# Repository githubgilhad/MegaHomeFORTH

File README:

Mega Home Computer with FORTH - based on ATmega2560 - step to graphic card for HD6309 - VGA, RCA, PS/2

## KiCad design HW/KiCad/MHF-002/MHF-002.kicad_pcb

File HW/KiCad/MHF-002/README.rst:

.. vim: ft=rst noexpandtab fileencoding=utf-8 nomodified   wrap textwidth=0 foldmethod=marker foldmarker={{{,}}} foldcolumn=4 ruler showcmd lcs=tab\:|- list tabstop=8 noexpandtab nosmarttab softtabstop=0 shiftwidth=0 linebreak showbreak=--»\ 

.. |Ohm| raw:: html

	Ω

.. |kOhm| raw:: html

	kΩ

|MemxFORTHChipandColorfulStack.png|

MegaHomeFORTH MHF-002
=====================

This is next iteration of `MegaHomeFORTH MHF-001 <https://github.com/githubgilhad/MegaHomeFORTH/tree/MHF-001>`__

MHF-001 was sponsored by PCBway.com, which generously manufactured the PCB for it as sponsorship. The PCB was perfectly done and allowed for testings and rewiring problematic parts to reveal hidden problems in the first iteration design.

MHF-002 have more than 75 improvements over MHF-001 and should be even more testable and more convenient for hand soldering, while using more modern parts.

Global Goals
============

|MHF-002.png|

|MHF-002.a.s.jpg|

|MHF-002.b.s.jpg|

MHF was created as an implementation of a graphical and I/O card design for an 8-bit computer based on the HD6309 processor (hereafter referred to as CPU). The actual design is built around the ATmega2560 microcontroller (used, for example, in the Arduino Mega), which I will refer to as the MCU. The MCU is supplemented with RAM and several simple circuits for input and output. Another RAM chip is used for data transfer in both directions, shared alternately between the CPU and MCU. The advantage of this design is high throughput (at the cost of latency) and easy access from both systems.

During the debugging of the preliminary prototypes, it proved to be a significant advantage to have interactive access to the hardware, which led to the implementation of FORTH. It also became clear that, in addition to VGA/RCA, the PS/2 keyboard and SD card could be read concurrently. With enough memory, the graphics card can even function as a standalone single-board computer (SBC), which is a more convenient mode for debugging.

Since access to the shared RAM requires cooperation with the GLUE, the board also includes jumpers for easy configuration of the SBC mode, where some signals intended for the SysBus are redirected directly to the shared memory.

Detailed configuration and usage options will be described on a separate page, but for a quick start, it is sufficient to solder either the left or right side of the A/B jumpers for the graphics card mode. For SBC mode, it is enough to solder the SBC jumpers. These options are mutually exclusive (either graphics card mode or SBC).

Next, there are previews of MHF-002 and links to the schematic and PCB (only the top and bottom layers, as both middle layers are reserved for power), which were generated from KiCad files.

.. |MHF-002.a.s.jpg| image:: MHF-002.a.s.jpg
	:width: 250
	:align: top
	:target: MHF-002.a.s.jpg

.. |MHF-002.b.s.jpg| image:: MHF-002.b.s.jpg
	:width: 250
	:align: top
	:target: MHF-002.b.s.jpg

.. |MHF-002.png| image:: MHF-002.png
	:width: 250
	:align: top
	:target: MHF-002.png

.. |MemxFORTHChipandColorfulStack.png| image:: MemxFORTHChipandColorfulStack.png
	:width: 250
	:align: top
	:target: MemxFORTHChipandColorfulStack.png

.. |view.bottom.png| image:: view.bottom.png
	:width: 250
	:align: top
	:target: view.bottom.png

.. |view_1.png| image:: view_1.png
	:width: 250
	:align: top
	:target: view_1.png

.. |view_2.png| image:: view_2.png
	:width: 250
	:align: top
	:target: view_2.png

.. |view_top.png| image:: view_top.png
	:width: 250
	:align: top
	:target: view_top.png

|view_top.png|

|view.bottom.png|

|view_1.png|

|view_2.png|

`Schema <schema.pdf>`__

`PCB <pcb.pdf>`__

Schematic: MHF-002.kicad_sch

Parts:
C1: 10nF; C_Disc_D4.3mm_W1.9mm_P5.00mm
C2, C5, C6, C7, C8, C10, C15, C16: 100n; C_0805_2012Metric_HandSolder
C3, C4: 22n; C_0805_2012Metric_HandSolder
C9: DTR 100n; C_Disc_D3.0mm_W2.0mm_P2.50mm
C11: 10M; C_0805_2012Metric_HandSolder
C12: 100n RESET; C_Disc_D3.0mm_W2.0mm_P2.50mm
C13, C14: 22p; C_0805_2012Metric_HandSolder
Cx1, Cx2, Cx3, Cx4, Cx5, Cx6, Cx7, Cx8, Cx9, Cx10, Cx11, Cx12, Cx13, Cx16, Cx17, Cx18: Cx; C_Disc_D3.0mm_W2.0mm_P2.50mm
Cx14, Cx15: Cx; CP_Radial_D5.0mm_P2.50mm
D1: 1N4001; D_DO-41_SOD81_P9.4mm_Horizontal
D2, D3: D; D_1210_3225Metric_HandSolder
D4, D5, D6, D7, D8, D9: WS2812B; LED_WS2812B_PLCC4_5.0x5.0mm_P3.2mm_HandSolder
D10: SS14; D_1812_4532Metric_Pad1.30x3.40mm_HandSolder
F1: Polyfuse; Fuse_1206_3216Metric_Pad1.42x1.75mm_HandSolder
H5, H6, H7, H8: MountingHole; MountingHole_3.2mm_M3_Pad
J1: VGA; DSUB-15-HD_Socket_Horizontal_P2.29x2.54mm_EdgePinOffset8.35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
J2: PS/2; J_Mini-DIN-6
J3: RCA; CUI_RCJ-047_Yellow
J4: SysBus; PinSocket_2x32_P2.54mm_Vertical
J5: Micro; USB_Micro-B_XKB_U254-051T-4BH83-F1S
J6: SysBus; PinHeader_2x32_P2.54mm_Vertical_down
J7: SPI; PinHeader_1x06_P2.54mm_Vertical
J8: ISP; PinHeader_2x03_P2.54mm_Vertical
J9: Serial; PinHeader_1x07_P2.54mm_Vertical
J10: I2C; PinHeader_1x04_P2.54mm_Vertical
J11: + 5V -; PinSocket_2x03_P2.54mm_Vertical
J12: Reset; PinHole_1x01_2.54xrectangle
J13, J110: +5V; PinHole_1x01_2.54xrectangle
J14, J108, J111, J112, J116: GND; PinHole_1x01_2.54xrectangle
J15: AREF; PinHole_1x01_2.54xrectangle
J16: XTAL2; PinHole_1x01_2.54xrectangle
J17: SDcard; PinHeader_1x06_P2.54mm_Vertical
J18: XTAL1; PinHole_1x01_2.54xrectangle
J19: AVCC; PinHole_1x01_2.54xrectangle
J20: RCAsel; PinHeader_1x03_P2.54mm_Vertical
J21, J22, J37, J38, J39, J40, J41, J42, J43, J44, J45, J46, J47, J48, J49, J50, J51, J52, J53, J54, J55, J56, J57, J58, J59, J60, J61, J62, J63, J64, J65, J66, J67, J68, J69, J70, J71, J72, J73, J74, J75, J76, J77, J78, J79, J80, J81, J82, J83, J84, J85, J86, J87, J88, J89, J90, J91, J92, J93, J94, J95, J96, J97, J98, J99, J100, J101, J102, J103, J104, J105, J106: x; PinHole_1x01_2.54xrectangle
J23: VIN 12V; BarrelJack_Horizontal
J24: AND_B1; PinHole_1x01_2.54xrectangle
J25: AND_B2; PinHole_1x01_2.54xrectangle
J26: AND_C1; PinHole_1x01_2.54xrectangle
J27: AND_C2; PinHole_1x01_2.54xrectangle
J28: AND_D1; PinHole_1x01_2.54xrectangle
J29: AND_D2; PinHole_1x01_2.54xrectangle
J30: AND_Dx; PinHole_1x01_2.54xrectangle
J31: AND_Cx; PinHole_1x01_2.54xrectangle
J32: AND_Bx; PinHole_1x01_2.54xrectangle
J33: NOTF; PinHole_1x01_2.54xrectangle
J34: NOTE; PinHole_1x01_2.54xrectangle
J35: NOTEx; PinHole_1x01_2.54xrectangle
J36: NOTFx; PinHole_1x01_2.54xrectangle
J107, J109: +3V3; PinHole_1x01_2.54xrectangle
J113: SDCard
J114: VIN; PinHole_1x01_2.54xrectangle
J115: VI; PinHole_1x01_2.54xrectangle
JP1: MISO; SolderJumper-2_P1.3mm_Bridged_Pad1.0x1.5mm
JP2: MOSI; SolderJumper-2_P1.3mm_Bridged_Pad1.0x1.5mm
JP3: SCK; SolderJumper-2_P1.3mm_Bridged_Pad1.0x1.5mm
JP4: SS; SolderJumper-2_P1.3mm_Bridged_Pad1.0x1.5mm
JP5: ANDB1+; SolderJumper-2_P1.3mm_Bridged_Pad1.0x1.5mm
JP6: ANDB2+; SolderJumper-2_P1.3mm_Bridged_Pad1.0x1.5mm
JP7: ANDC1+; SolderJumper-2_P1.3mm_Bridged_Pad1.0x1.5mm
JP8: ANDC2+; SolderJumper-2_P1.3mm_Bridged_Pad1.0x1.5mm
JP9: ANDD1+; SolderJumper-2_P1.3mm_Bridged_Pad1.0x1.5mm
JP10: ANDD2+; SolderJumper-2_P1.3mm_Bridged_Pad1.0x1.5mm
JP11: NOTF; SolderJumper-2_P1.3mm_Bridged_Pad1.0x1.5mm
JP12: HaltLED; SolderJumper-2_P1.3mm_Bridged_Pad1.0x1.5mm
JP13: XHalt; SolderJumper-2_P1.3mm_Bridged_Pad1.0x1.5mm
JP14: xAVCC; SolderJumper-2_P1.3mm_Bridged_Pad1.0x1.5mm
JP15: TX340; SolderJumper-2_P1.3mm_Open_RoundedPad1.0x1.5mm
JP16: RX340; SolderJumper-2_P1.3mm_Open_RoundedPad1.0x1.5mm
JP17: CTS340; SolderJumper-2_P1.3mm_Open_RoundedPad1.0x1.5mm
JP18: DTR340; SolderJumper-2_P1.3mm_Open_RoundedPad1.0x1.5mm
JP19: RTS340; SolderJumper-2_P1.3mm_Open_RoundedPad1.0x1.5mm
JP20: USB_GND; G_Rework_Jumper_Bridged_2.54mm
JP21: RX0; SolderJumper-2_P1.3mm_Open_RoundedPad1.0x1.5mm
JP22: TX0; SolderJumper-2_P1.3mm_Open_RoundedPad1.0x1.5mm
JP23: RTS0; SolderJumper-2_P1.3mm_Open_RoundedPad1.0x1.5mm
JP24: DTR0; SolderJumper-2_P1.3mm_Open_RoundedPad1.0x1.5mm
JP25: CTS0; SolderJumper-2_P1.3mm_Open_RoundedPad1.0x1.5mm
JP26: PS2; PinHeader_1x02_P2.54mm_Vertical
JP27: VGA; PinHeader_1x06_P2.54mm_Vertical
JP28: RCA; PinHeader_1x02_P2.54mm_Vertical
JP29: SBC_D_Dir; SolderJumper-2_P1.3mm_Open_RoundedPad1.0x1.5mm
JP30: USB_PWR; G_Rework_Jumper_Bridged_2.54mm
JP31: USB_D+; G_Rework_Jumper_Bridged_2.54mm
JP32: USB_D-; G_Rework_Jumper_Bridged_2.54mm
JP33: SBC_A_DIR; SolderJumper-2_P1.3mm_Open_RoundedPad1.0x1.5mm
JP34: SBC_G_Enable; SolderJumper-2_P1.3mm_Open_RoundedPad1.0x1.5mm
JP35: SBC_S_SELECT; SolderJumper-2_P1.3mm_Open_RoundedPad1.0x1.5mm
JP36: SBC_Read; SolderJumper-2_P1.3mm_Open_RoundedPad1.0x1.5mm
JP37: SBC_Write; SolderJumper-2_P1.3mm_Open_RoundedPad1.0x1.5mm
JP38: SHSelect; SolderJumper-3_P1.3mm_Open_RoundedPad1.0x1.5mm
JP55: PS2_Data; SolderJumper-2_P1.3mm_Open_RoundedPad1.0x1.5mm
JP56: PS2_CLK; SolderJumper-2_P1.3mm_Open_RoundedPad1.0x1.5mm
JP91: Inside; SolderJumper-2_P1.3mm_Bridged_Pad1.0x1.5mm
JP92: X_S16; SolderJumper-3_P1.3mm_Open_RoundedPad1.0x1.5mm
JP94: A_HALT; SolderJumper-3_P1.3mm_Open_RoundedPad1.0x1.5mm
JP95: A_READ; SolderJumper-3_P1.3mm_Open_RoundedPad1.0x1.5mm
JP98: SHDirty; SolderJumper-3_P1.3mm_Open_RoundedPad1.0x1.5mm
JP99: SHGranted; SolderJumper-3_P1.3mm_Open_RoundedPad1.0x1.5mm
JP100: SHRequest; SolderJumper-3_P1.3mm_Open_RoundedPad1.0x1.5mm
JP102: S_SELECT; SolderJumper-3_P1.3mm_Open_RoundedPad1.0x1.5mm
JP103: S_Read; SolderJumper-3_P1.3mm_Open_RoundedPad1.0x1.5mm
JP104: S_Write; SolderJumper-3_P1.3mm_Open_RoundedPad1.0x1.5mm
JP105: GDdir; SolderJumper-3_P1.3mm_Open_RoundedPad1.0x1.5mm
JP106: GEnable; SolderJumper-3_P1.3mm_Open_RoundedPad1.0x1.5mm
JP107: GADir; SolderJumper-3_P1.3mm_Open_RoundedPad1.0x1.5mm
LED1: RX0; LED_0805_2012Metric
LED2: TX0; LED_0805_2012Metric
LED3: ON; LED_0805_2012Metric
LED4: CTS0; LED_0805_2012Metric
LED5: RTS0; LED_0805_2012Metric
LED6: SCL; LED_0805_2012Metric
LED7: SPI; LED_0805_2012Metric
LED8: HALT; LED_0805_2012Metric
LED9: SYSTEM; LED_0805_2012Metric
LED10: Reset; LED_0805_2012Metric
M1: CP2102; G_CP2102
M3, M5: CY7C109D-10ZXI; G_TSOP-I-32_18.4x8mm_HandSolder
PA1: PA; PinHeader_1x09_P2.54mm_Vertical
PB1: PB; PinHeader_1x09_P2.54mm_Vertical
PC1: PC; PinHeader_1x09_P2.54mm_Vertical
PD1: PD; PinHeader_1x09_P2.54mm_Vertical
PE1: PE; PinHeader_1x09_P2.54mm_Vertical
PF1: PF; PinHeader_1x09_P2.54mm_Vertical
PG1: PG; PinHeader_1x07_P2.54mm_Vertical
PH1: PH; PinHeader_1x09_P2.54mm_Vertical
PJ1: PJ; PinHeader_1x09_P2.54mm_Vertical
PK1: PK; PinHeader_1x09_P2.54mm_Vertical
PL1: PL; PinHeader_1x09_P2.54mm_Vertical
Q1: S8050; TO-92_Inline
Q2: 2907; TSOT-23_HandSoldering
R1: 20k; R_0805_2012Metric_Pad1.20x1.40mm_HandSolder
R2: 440; R_0805_2012Metric_Pad1.20x1.40mm_HandSolder
R3, R28, R36, R37, R38, R39, R40, R41, R42, R43, R46, R48, R49: 1k; R_0805_2012Metric_Pad1.20x1.40mm_HandSolder
R4: 1k3; R_0805_2012Metric_Pad1.20x1.40mm_HandSolder
R5, R16, R17, R18, R19, R20, R21, R22, R23, R26, R44, R45, R47: 10k; R_0805_2012Metric_Pad1.20x1.40mm_HandSolder
R6, R7, R8: 1k2; R_0805_2012Metric_Pad1.20x1.40mm_HandSolder
R9, R10, R11: 680; R_0805_2012Metric_Pad1.20x1.40mm_HandSolder
R12, R13: 3k3; R_0805_2012Metric_Pad1.20x1.40mm_HandSolder
R14, R15: 75; R_0805_2012Metric_Pad1.20x1.40mm_HandSolder
R24, R25, R30, R31: 22; R_0805_2012Metric_Pad1.20x1.40mm_HandSolder
R27, R29: 1M; R_0805_2012Metric_Pad1.20x1.40mm_HandSolder
R32, R33: 4k7; R_0805_2012Metric_Pad1.20x1.40mm_HandSolder
R34, R35: 6k8; R_0805_2012Metric_Pad1.20x1.40mm_HandSolder
R50: 0?; R_0805_2012Metric_Pad1.20x1.40mm_HandSolder
S1: Reset; G_Arduino_switch; PARTREV 1.0
TP1: 7; TestPoint_Pad_1.0x1.0mm
TP2: 0; TestPoint_Pad_1.0x1.0mm
TP3: 1; TestPoint_Pad_1.0x1.0mm
TP4: 2; TestPoint_Pad_1.0x1.0mm
TP5: 3; TestPoint_Pad_1.0x1.0mm
TP6: 4; TestPoint_Pad_1.0x1.0mm
TP7: 5; TestPoint_Pad_1.0x1.0mm
TP8: 6; TestPoint_Pad_1.0x1.0mm
U1: ATMEGA2560; G_TQFP-100_14x14mm_HandSolder
U2: 74HC14; SOIC-14_3.9x8.7mm_P1.27mm
U3: 74HC08; SOIC-14_3.9x8.7mm_P1.27mm
U4: 74AHC573; TSSOP-20_4.4x6.5mm_P0.65mm_HandSolder
U5: 74HC166; SOIC-16_3.9x9.9mm_P1.27mm
U7, U8: 74HC595; SOIC-16_3.9x9.9mm_P1.27mm
U9: 74HC157; SOIC-16_3.9x9.9mm_P1.27mm
U10, U11, U12: 74HC245; G_SOIC-20W_7.5x12.8mm_P1.27mm_HandSolder
U13: CH340G; SOIC-16_3.9x9.9mm_P1.27mm
U14: AMS1117-5.0; SOT-223-3_TabPin2_HandSolder
U15: AMS1117-3.3; SOT-223-3_TabPin2_HandSolder
Y1: 16 MHz; Crystal_SMD_HC49-SD
Y2: 12 MHz; Crystal_SMD_HC49-SD

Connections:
16MHz: PE1.8, U1.9 ((CLKO/ICP3/INT7)PE7), U5.7 (Clk)
+3.3V: C16.1, J107.1, J109.1, U15.2 (VO)
+5V: C6.1, C7.1, C8.1, C10.1, C15.1, Cx1.1, Cx2.1, Cx3.1, Cx4.1, Cx5.1, Cx6.1, Cx7.1, Cx8.1, Cx9.1, Cx10.1, Cx11.1, Cx12.1, Cx13.1, Cx14.1, Cx15.1, Cx16.1, Cx17.1, Cx18.1, D2.1 (K), D4.1 (VDD), D5.1 (VDD), D6.1 (VDD), D7.1 (VDD), D8.1 (VDD), D9.1 (VDD), F1.1, J2.4, J4.1, J4.2, J6.1, J6.2, J7.5, J8.2 (VCC), J9.7, J10.2, J11.1, J11.3, J11.5, J13.1, J17.5, J110.1, J113.5 (VCC), JP5.1 (A), JP6.1 (A), JP7.1 (A), JP8.1 (A), JP9.1 (A), JP10.1 (A), JP11.1 (A), JP14.1 (A), M1.8 (+5V), M3.6 (CS2/CE2), M3.8 (VCC), M5.6 (CS2/CE2), M5.8 (VCC), R3.2, R5.2, R12.2, R13.2, R26.1, R32.1, R33.1, R34.2, R35.2, R36.2, R39.2, R42.1, R47.2, R50.1, U1.10 (VCC), U1.31 (VCC1), U1.61 (VCC2), U1.80 (VCC3), U2.14 (VCC), U3.14 (VCC), U4.20 (VCC), U5.9 (Clr), U5.16 (VCC), U7.10 (~SRCLR), U7.16 (VCC), U8.10 (~SRCLR), U8.16 (VCC), U9.16 (VCC), U11.20 (VCC), U12.20 (VCC), U13.16 (VCC), U14.2 (VO), U15.3 (VI)
/A_16: J4.27, J6.27, JP92.1 (A)
/B_16: J4.28, J6.28, JP92.3 (B)
/L0: M3.16 (A4), TP2.1, U4.12 (Q7)
/L1: M3.15 (A5), TP3.1, U4.13 (Q6)
/L2: M3.14 (A6), TP4.1, U4.14 (Q5)
/L3: M3.13 (A7), TP5.1, U4.15 (Q4)
/L4: M3.17 (A3), TP6.1, U4.16 (Q3)
/L5: M3.18 (A2), TP7.1, U4.17 (Q2)
/L6: M3.19 (A1), TP8.1, U4.18 (Q1)
/L7: M3.20 (A0), TP1.1, U4.19 (Q0)
/L-on: LED3.2 (A), R36.1
/L-rx: LED1.2 (A), R34.1
/L-tx: LED2.2 (A), R35.1
/L_13: LED4.2 (A), R37.1
/RCA_Output: J3.1 (In), JP28.1, Q1.3 (C), R2.2, R3.1
A0: J4.11, J6.11, U11.18 (B0)
A1: J4.12, J6.12, U11.17 (B1)
A2: J4.13, J6.13, U11.16 (B2)
A3: J4.14, J6.14, U11.15 (B3)
A4: J4.15, J6.15, U11.14 (B4)
A5: J4.16, J6.16, U11.13 (B5)
A6: J4.17, J6.17, U11.12 (B6)
A7: J4.18, J6.18, U11.11 (B7)
A8: J4.19, J6.19, U12.18 (B0)
A9: J4.20, J6.20, U12.17 (B1)
A10: J4.21, J6.21, U12.16 (B2)
A11: J4.22, J6.22, U12.15 (B3)
A12: J4.23, J6.23, U12.14 (B4)
A13: J4.24, J6.24, U12.13 (B5)
A14: J4.25, J6.25, U12.12 (B6)
A15: J4.26, J6.26, U12.11 (B7)
ALE: PG1.3, U1.70 ((ALE)PG2), U4.11 (Load)
AREF: C5.1, J15.1, U1.98 (AREF)
A_G_A_DIR: J4.47, J6.47, JP107.1 (A)
A_G_D_DIR: J4.49, J6.49, JP105.1 (A)
A_G_ENABLE: J4.45, J6.45, JP106.1 (A)
A_HALT: J4.29, J6.29, JP94.1 (A)
A_READ: J4.31, J6.31, JP95.1 (A)
A_SHARE_DIRTY: J4.33, J6.33, JP98.1 (A)
A_SHARE_GRANTED: J4.35, J6.35, JP99.1 (A)
A_SHARE_REQUEST: J4.37, J6.37, JP100.1 (A)
A_SHARE_SELECT: J4.51, J6.51, JP38.1 (A)
A_S_READ: J4.41, J6.41, JP103.1 (A)
A_S_SELECT: J4.39, J6.39, JP102.1 (A)
A_S_WRITE: J4.43, J6.43, JP104.1 (A)
B_G_A_DIR: J4.48, J6.48, JP107.3 (B)
B_G_D_DIR: J4.50, J6.50, JP105.3 (B)
B_G_ENABLE: J4.46, J6.46, JP106.3 (B)
B_HALT: J4.30, J6.30, JP94.3 (B)
B_READ: J4.32, J6.32, JP95.3 (B)
B_SHARE_DIRTY: J4.34, J6.34, JP98.3 (B)
B_SHARE_GRANTED: J4.36, J6.36, JP99.3 (B)
B_SHARE_REQUEST: J4.38, J6.38, JP100.3 (B)
B_SHARE_SELECT: J4.52, J6.52, JP38.3 (B)
B_S_READ: J4.42, J6.42, JP103.3 (B)
B_S_SELECT: J4.40, J6.40, JP102.3 (B)
B_S_WRITE: J4.44, J6.44, JP104.3 (B)
Bb: PH1.2, U1.13 (PH1(TXD2)), U9.14 (I0d)
Bf: PH1.6, U1.17 (PH5(OC4C)), U9.13 (I1d)
Blue: J1.3, JP27.3, R8.2, R11.2
CTS0: J9.2, JP19.2 (B), JP25.2 (B), PB1.5, R37.2, U1.23 ((OC2A/PCINT4)PB4)
D0: J4.3, J6.3, U10.18 (B0)
D1: J4.4, J6.4, U10.17 (B1)
D2: J4.5, J6.5, U10.16 (B2)
D3: J4.6, J6.6, U10.15 (B3)
D4: J4.7, J6.7, U10.14 (B4)
D5: J4.8, J6.8, U10.13 (B5)
D6: J4.9, J6.9, U10.12 (B6)
D7: J4.10, J6.10, U10.11 (B7)
DTR: C9.2, J9.3, JP18.2 (B), JP24.2 (B), R28.2
Debug_LEDs: D4.4 (DIN), R49.2
GND: C1.2, C2.1, C3.1, C4.1, C5.2, C6.2, C7.2, C8.2, C10.2, C11.2, C12.2, C13.1, C14.1, C15.2, C16.2, Cx1.2, Cx2.2, Cx3.2, Cx4.2, Cx5.2, Cx6.2, Cx7.2, Cx8.2, Cx9.2, Cx10.2, Cx11.2, Cx12.2, Cx13.2, Cx14.2, Cx15.2, Cx16.2, Cx17.2, Cx18.2, D4.3 (VSS), D5.3 (VSS), D6.3 (VSS), D7.3 (VSS), D8.3 (VSS), D9.3 (VSS), J1.0, J1.5, J1.6, J1.7, J1.8, J1.10, J2.3, J2.S (Shield), J3.2 (Ext), J4.63, J4.64, J6.63, J6.64, J7.6, J8.6 (GND), J9.6, J10.1, J11.2, J11.4, J11.6, J14.1, J17.6, J23.2, J23.3, J108.1, J111.1, J112.1, J113.6 (GND), J116.1, JP20.2 (B), JP27.6, JP28.2, LED3.1 (K), LED4.1 (K), LED5.1 (K), LED7.1 (K), LED8.1 (K), LED9.1 (K), M1.9 (GND), M3.24 (GND), M3.30 (~CS1/~CE1), M5.24 (GND), PA1.9, PB1.9, PC1.9, PD1.9, PE1.9, PF1.9, PG1.7, PH1.9, PJ1.9, PK1.9, PL1.9, Q1.1 (E), Q2.3 (C), R28.1, R40.1, S1.3 (K), S1.4 (A), U1.11 (GND), U1.32 (GND1), U1.62 (GND2), U1.81 (GND3), U1.99 (AGND), U2.7 (GND), U3.7 (GND), U4.1 (OE), U4.10 (GND), U5.6 (CE), U5.8 (GND), U7.8 (GND), U8.8 (GND), U9.8 (GND), U10.10 (GND), U11.10 (GND), U12.10 (GND), U13.1 (GND), U14.1 (GND), U15.1 (GND)
G_A_DIR: JP33.2 (B), JP107.2 (C), U11.1 (A->B), U12.1 (A->B)
G_D_DIR: JP29.2 (B), JP105.2 (C), U10.1 (A->B)
G_ENABLE: JP34.2 (B), JP106.2 (C), U10.19 (CE), U11.19 (CE), U12.19 (CE)
Gb: PH1.3, U1.14 (PH2(XCK2)), U9.11 (I0c)
Gf: PH1.7, U1.18 (PH6(OC2B)), U9.10 (I1c)
Green: J1.2, JP27.4, R7.2, R10.2
HSyncVGA_SuppressRCA: PB1.7, R14.2, U1.25 ((OC1B/PCINT6)PB6), U3.2
Ib: PH1.1, U1.12 (PH0(RXD2)), U9.2 (I0a)
If: PH1.5, U1.16 (PH4(OC4B)), U9.3 (I1a)
Inside: JP91.2 (B), PE1.7, U1.8 ((T3/INT6)PE6)
MISO: J7.4, J8.1 (MISO), JP1.2 (B), JP55.1 (A), PB1.4, U1.22 ((MISO/PCINT3)PB3)
MOSI: J7.3, J8.4 (MOSI), JP2.2 (B), JP56.1 (A), PB1.3, U1.21 ((MOSI/PCINT2)PB2)
MasterReset: D10.1 (K), J4.62, J6.62
unnamed: C1.1, D1.2 (A), R1.1, U2.5
unnamed: C11.1, D3.1 (K), J115.1, U14.3 (VI)
unnamed: D4.2 (DOUT), D5.4 (DIN)
unnamed: D5.2 (DOUT), D6.4 (DIN)
unnamed: D6.2 (DOUT), D7.4 (DIN)
unnamed: D7.2 (DOUT), D8.4 (DIN)
unnamed: D8.2 (DOUT), D9.4 (DIN)
unnamed: J5.3 (D+), JP31.1 (A)
unnamed: J5.2 (D-), JP32.1 (A)
unnamed: J5.5 (GND), J5.6 (Shield), JP20.1 (A)
unnamed: J5.1 (VBUS), JP30.1 (A)
unnamed: J19.1, JP14.2 (B), U1.100 (AVCC)
unnamed: J20.2, R5.1, U3.1
unnamed: J20.3, U5.13 (Qh), U9.1 (S)
unnamed: J24.1, JP5.2 (B), U3.4
unnamed: J25.1, JP6.2 (B), U3.5
unnamed: J26.1, JP7.2 (B), U3.9
unnamed: J27.1, JP8.2 (B), U3.10
unnamed: J28.1, JP9.2 (B), U3.12
unnamed: J29.1, JP10.2 (B), U3.13
unnamed: J30.1, U3.11
unnamed: J31.1, U3.8
unnamed: J32.1, U3.6
unnamed: J33.1, JP11.2 (B), U2.13
unnamed: J34.1, JP12.2 (B), U2.11
unnamed: J35.1, R43.2, U2.10
unnamed: J36.1, U2.12
unnamed: J17.1, J113.1 (CS), JP4.1 (A)
unnamed: J17.4, J113.4 (MISO), JP1.1 (A)
unnamed: J17.3, J113.3 (MOSI), JP2.1 (A)
unnamed: J17.2, J113.2 (SCK), JP3.1 (A)
unnamed: JP12.1 (A), JP13.1 (A), PE1.6, U1.7 ((OC3C/INT5)PE5)
unnamed: JP15.1 (A), R30.1
unnamed: JP16.1 (A), R31.1
unnamed: JP17.1 (A), U13.9 (~CTS)
unnamed: JP18.1 (A), U13.13 (~DTR)
unnamed: JP19.1 (A), U13.14 (~RTS)
unnamed: JP21.1 (A), M1.7 (TXD)
unnamed: JP22.1 (A), M1.6 (RXD)
unnamed: JP23.1 (A), M1.4 (CTS)
unnamed: JP24.1 (A), M1.5 (DTR)
unnamed: JP25.1 (A), M1.3 (RTS)
unnamed: J2.5, JP26.1, R13.1, U2.1
unnamed: J1.14, JP27.1, R15.1
unnamed: J1.13, JP27.2, R14.1
unnamed: F1.2, JP30.2 (B)
unnamed: JP31.2 (B), R24.2
unnamed: JP32.2 (B), R25.2
unnamed: JP55.2 (B), R45.1
unnamed: JP56.2 (B), R44.1
unnamed: JP91.1 (A), U2.6
unnamed: LED5.2 (A), R38.1
unnamed: LED6.2 (A), R39.1
unnamed: LED6.1 (K), Q2.2 (E)
unnamed: LED7.2 (A), R41.1
unnamed: LED8.2 (A), R43.1
unnamed: LED9.2 (A), R46.1
unnamed: LED10.2 (A), R47.1
unnamed: PD1.5, R48.1, R49.1, U1.47 ((ICP1)PD4)
unnamed: PD1.6, U1.48 ((XCK1)PD5)
unnamed: Q1.2 (B), R4.2
unnamed: R2.1, U3.3
unnamed: R4.1, U2.8
unnamed: U7.9 (QH'), U8.14 (SER)
unnamed: U2.2, U2.3, U7.11 (SRCLK), U8.11 (SRCLK)
unnamed: R6.1, R7.1, R8.1, U9.4 (Za)
unnamed: R9.1, U9.7 (Zb)
unnamed: R10.1, U9.9 (Zc)
unnamed: R11.1, U9.12 (Zd)
unnamed: R50.2, U10.20 (VCC)
unnamed: R31.2, U13.3 (RXD)
unnamed: R30.2, U13.2 (TXD)
unnamed: C2.2, U13.4 (V3)
unnamed: C4.2, R27.1, U13.7 (XI), Y2.2
unnamed: C3.2, R27.2, U13.8 (XO), Y2.1
PS2 Clock: D1.1 (K), R1.2, R44.2, U2.4, U7.12 (RCLK), U8.12 (RCLK)
PS2 Data: J2.1, JP26.2, R12.1, R45.2, U7.14 (SER)
PS2-OE: PE1.3, U1.4 ((XCK0/AIN0)PE2), U7.13 (~OE), U8.13 (~OE)
PSDat0: R16.1, U8.1 (QB)
PSDat1: R17.1, U8.15 (QA)
PSDat2: R18.1, U7.7 (QH)
PSDat3: R19.1, U7.6 (QG)
PSDat4: R20.1, U7.5 (QF)
PSDat5: R21.1, U7.4 (QE)
PSDat6: R22.1, U7.3 (QD)
PSDat7: R23.1, U7.2 (QC)
RD: M3.32 (~OE), PG1.2, U1.52 ((RD)PG1)
RD+: R24.1, U13.5 (UD+)
RD-: R25.1, U13.6 (UD-)
RTS0: J9.1, JP17.2 (B), JP23.2 (B), PB1.6, R38.2, U1.24 ((OC1A/PCINT5)PB5)
RX0: J9.4, JP15.2 (B), JP21.2 (B), LED1.1 (K), PE1.1, U1.2 ((RXD0/PCIN8)PE0)
Rb: PH1.4, U1.15 (PH3(OC4A)), U9.5 (I0b)
Red: J1.1, JP27.5, R6.2, R9.2
Reset: C9.1, C12.1, D2.2 (A), D10.2 (A), J8.5 (~RST), J12.1, LED10.1 (K), R26.2, S1.1, S1.2, U1.30 (RESET)
Rf: PH1.8, U1.27 (PH7(T4)), U9.6 (I1b)
SCK: J7.2, J8.3 (SCK), JP3.2 (B), PB1.2, R41.2, U1.20 ((SCK/PCINT1)PB1)
SCL: J10.4, PD1.1, Q2.1 (B), R33.2, U1.43 ((SCL/INT0)PD0)
SDA: J10.3, PD1.2, R32.2, U1.44 ((SDA/INT1)PD1)
SIGNAL_RCA: J20.1, PD1.4, U1.46 ((TXD1/INT3)PD3)
SS: J7.1, JP4.2 (B), PB1.1, U1.19 ((SS/PCINT0)PB0)
S_READ: JP36.2 (B), JP103.2 (C), M5.32 (~OE)
S_SELECT: JP35.2 (B), JP102.2 (C), M5.30 (~CS1/~CE1)
S_WRITE: JP37.2 (B), JP104.2 (C), M5.5 (~WE)
Shared_Address_A0: M5.20 (A0), PJ1.1, U1.63 (PJ0(RXD3/PCINT9)), U11.2 (A0)
Shared_Address_A1: M5.19 (A1), PJ1.2, U1.64 (PJ1(TXD3/PCINT10)), U11.3 (A1)
Shared_Address_A2: M5.18 (A2), PJ1.3, U1.65 (PJ2(XCK3/PCINT11)), U11.4 (A2)
Shared_Address_A3: M5.17 (A3), PJ1.4, U1.66 (PJ3(PCINT12)), U11.5 (A3)
Shared_Address_A4: M5.13 (A7), PJ1.5, U1.67 (PJ4(PCINT13)), U11.6 (A4)
Shared_Address_A5: M5.14 (A6), PJ1.6, U1.68 (PJ5(PCINT14)), U11.7 (A5)
Shared_Address_A6: M5.15 (A5), PJ1.7, U1.69 (PJ6(PCINT15)), U11.8 (A6)
Shared_Address_A7: M5.16 (A4), PJ1.8, U1.79 (PJ7), U11.9 (A7)
Shared_Address_A8: M5.1 (A11), PK1.1, U1.89 (PK0(ADC8/PCINT16)), U12.2 (A0)
Shared_Address_A9: M5.2 (A9), PK1.2, U1.88 (PK1(ADC9/PCINT17)), U12.3 (A1)
Shared_Address_A10: M5.3 (A8), PK1.3, U1.87 (PK2(ADC10/PCINT18)), U12.4 (A2)
Shared_Address_A11: M5.4 (A13), PK1.4, U1.86 (PK3(ADC11/PCINT19)), U12.5 (A3)
Shared_Address_A12: M5.7 (A15), PK1.5, U1.85 (PK4(ADC12/PCINT20)), U12.6 (A4)
Shared_Address_A13: M5.11 (A14), PK1.6, U1.84 (PK5(ADC13/PCINT21)), U12.7 (A5)
Shared_Address_A14: M5.12 (A12), PK1.7, U1.83 (PK6(ADC14/PCINT22)), U12.8 (A6)
Shared_Address_A15: M5.31 (A10), PK1.8, U1.82 (PK7(ADC15/PCINT23)), U12.9 (A7)
Shared_data_D0: M5.29 (DQ7), PL1.1, U1.35 (PL0(ICP4)), U10.2 (A0)
Shared_data_D1: M5.28 (DQ6), PL1.2, U1.36 (PL1(ICP5)), U10.3 (A1)
Shared_data_D2: M5.27 (DQ5), PL1.3, U1.37 (PL2(T5)), U10.4 (A2)
Shared_data_D3: M5.26 (DQ4), PL1.4, U1.38 (PL3(OC5A)), U10.5 (A3)
Shared_data_D4: M5.25 (DQ3), PL1.5, U1.39 (PL4(OC5B)), U10.6 (A4)
Shared_data_D5: M5.23 (DQ2), PL1.6, U1.40 (PL5(OC5C)), U10.7 (A5)
Shared_data_D6: M5.22 (DQ1), PL1.7, U1.41 (PL6), U10.8 (A6)
Shared_data_D7: M5.21 (DQ0), PL1.8, U1.42 (PL7), U10.9 (A7)
TX0: J9.5, JP16.2 (B), JP22.2 (B), LED2.1 (K), PE1.2, U1.3 ((TXD0)PE1)
VGA Latch: PB1.8, R46.2, U1.26 ((OC0A/OC1C/PCINT7)PB7), U5.15 (PE)
VGA data 0: PF1.1, R16.2, U1.97 ((ADC0)PF0), U5.2 (A)
VGA data 1: PF1.2, R17.2, U1.96 ((ADC1)PF1), U5.3 (B)
VGA data 2: PF1.3, R18.2, U1.95 ((ADC2)PF2), U5.4 (C)
VGA data 3: PF1.4, R19.2, U1.94 ((ADC3)PF3), U5.5 (D)
VGA data 4: PF1.5, R20.2, U1.93 ((ADC4/TCK)PF4), U5.10 (E)
VGA data 5: PF1.6, R21.2, U1.92 ((ADC5/TMS)PF5), U5.11 (F)
VGA data 6: PF1.7, R22.2, U1.91 ((ADC6/TDO)PF6), U5.12 (G)
VGA data 7: PF1.8, R23.2, U1.90 ((ADC7/TDI)PF7), U5.14 (H)
VIN: D3.2 (A), J23.1, J114.1
VSyncVGA_RCA: PE1.5, R15.2, U1.6 ((OC3B/INT4)PE4), U2.9
WE: M3.5 (~WE), PG1.1, U1.51 ((WR)PG0)
XAA0: M3.1 (A11), PC1.1, U1.53 ((A8)PC0)
XAA1: M3.2 (A9), PC1.2, U1.54 ((A9)PC1)
XAA2: M3.3 (A8), PC1.3, U1.55 ((A10)PC2)
XAA3: M3.4 (A13), PC1.4, U1.56 ((A11)PC3)
XAA4: M3.7 (A15), PC1.5, U1.57 ((A12)PC4)
XAA5: M3.11 (A14), PC1.6, U1.58 ((A13)PC5)
XAA6: M3.12 (A12), PC1.7, U1.59 ((A14)PC6)
XAA7: M3.31 (A10), PC1.8, U1.60 ((A15)PC7)
XAA16: M3.10 (A16), PG1.4, U1.28 ((TOSC2)PG3)
XAD0: M3.21 (DQ0), PA1.1, U1.78 ((AD0)PA0), U4.9 (D7)
XAD1: M3.22 (DQ1), PA1.2, U1.77 ((AD1)PA1), U4.8 (D6)
XAD2: M3.23 (DQ2), PA1.3, U1.76 ((AD2)PA2), U4.7 (D5)
XAD3: M3.25 (DQ3), PA1.4, U1.75 ((AD3)PA3), U4.6 (D4)
XAD4: M3.26 (DQ4), PA1.5, U1.74 ((AD4)PA4), U4.5 (D3)
XAD5: M3.27 (DQ5), PA1.6, U1.73 ((AD5)PA5), U4.4 (D2)
XAD6: M3.28 (DQ6), PA1.7, U1.72 ((AD6)PA6), U4.3 (D1)
XAD7: M3.29 (DQ7), PA1.8, U1.71 ((AD7)PA7), U4.2 (D0)
XTAL1: C13.2, J18.1, R29.1, U1.33 (XTAL2), Y1.2
XTAL2: C14.2, J16.1, R29.2, U1.34 (XTAL1), Y1.1
X_HALT: JP13.2 (B), JP37.1 (A), JP94.2 (C), R40.2, R42.2
X_READ: JP36.1 (A), JP95.2 (C), PD1.8, U1.50 ((T0)PD7)
X_S16: JP92.2 (C), M5.10 (A16), PE1.4, U1.5 ((OC3A/AIN1)PE3)
X_SHARE_DIRTY: JP34.1 (A), JP98.2 (C), PD1.7, U1.49 ((T1)PD6)
X_SHARE_GRANTED: JP29.1 (A), JP99.2 (C), R48.2
X_SHARE_REQUEST: JP33.1 (A), JP100.2 (C), PG1.5, U1.29 ((TOSC1)PG4)
X_SHARE_SELECT: JP35.1 (A), JP38.2 (C), PG1.6, U1.1 ((OC0B)PG5)
~VGA_Enable: PD1.3, U1.45 ((RXD1/INT2)PD2), U9.15 (E)

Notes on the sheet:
<-- Stop bit (1)
ATMEGA D[0..7]
Facts: NOT = delay 7-14 ns PS/2 = clock at least 30us down 30 us up 595 = SER before SRCLK^ min 25 ns SRCLK^ before RCLK^ min 19 ns SER after SRCLK^ min 0ns Strategy: negate CLK to have RSCLK^ for 595 negate RSCLK again for RCLK^ data latched (min 30us after RSCLK^ >> 19ns)
Data
SDA
<-- LSB
RX for Signal_RCA
Input / Output connector
EMS RAM 8000-9FFF A000-BFFFF (shared between Arduino and HD6309)
<-- Start bit (0)
JUNK (end of prev frame)
ATMEGA A[8..15]
I2C: GND VCC SDA SCL
PB7 is usual Arduino Mega SYSTEM_LED - with VGA it will shine full time
VGA Colors
Clock
External RAM for Arduino
SCL
ATMEGA A[0..7]
POZOR delic 440 x 1k je vypoctena hodnota (R2 R3)
SCK for Signal_RCA
came first
came last
10-20 Ohm, or diode for restricting voltage and lowering ViH under 3.4V
<-- Parity (= parity+data should be odd)
<-- MSB
Shared Memory

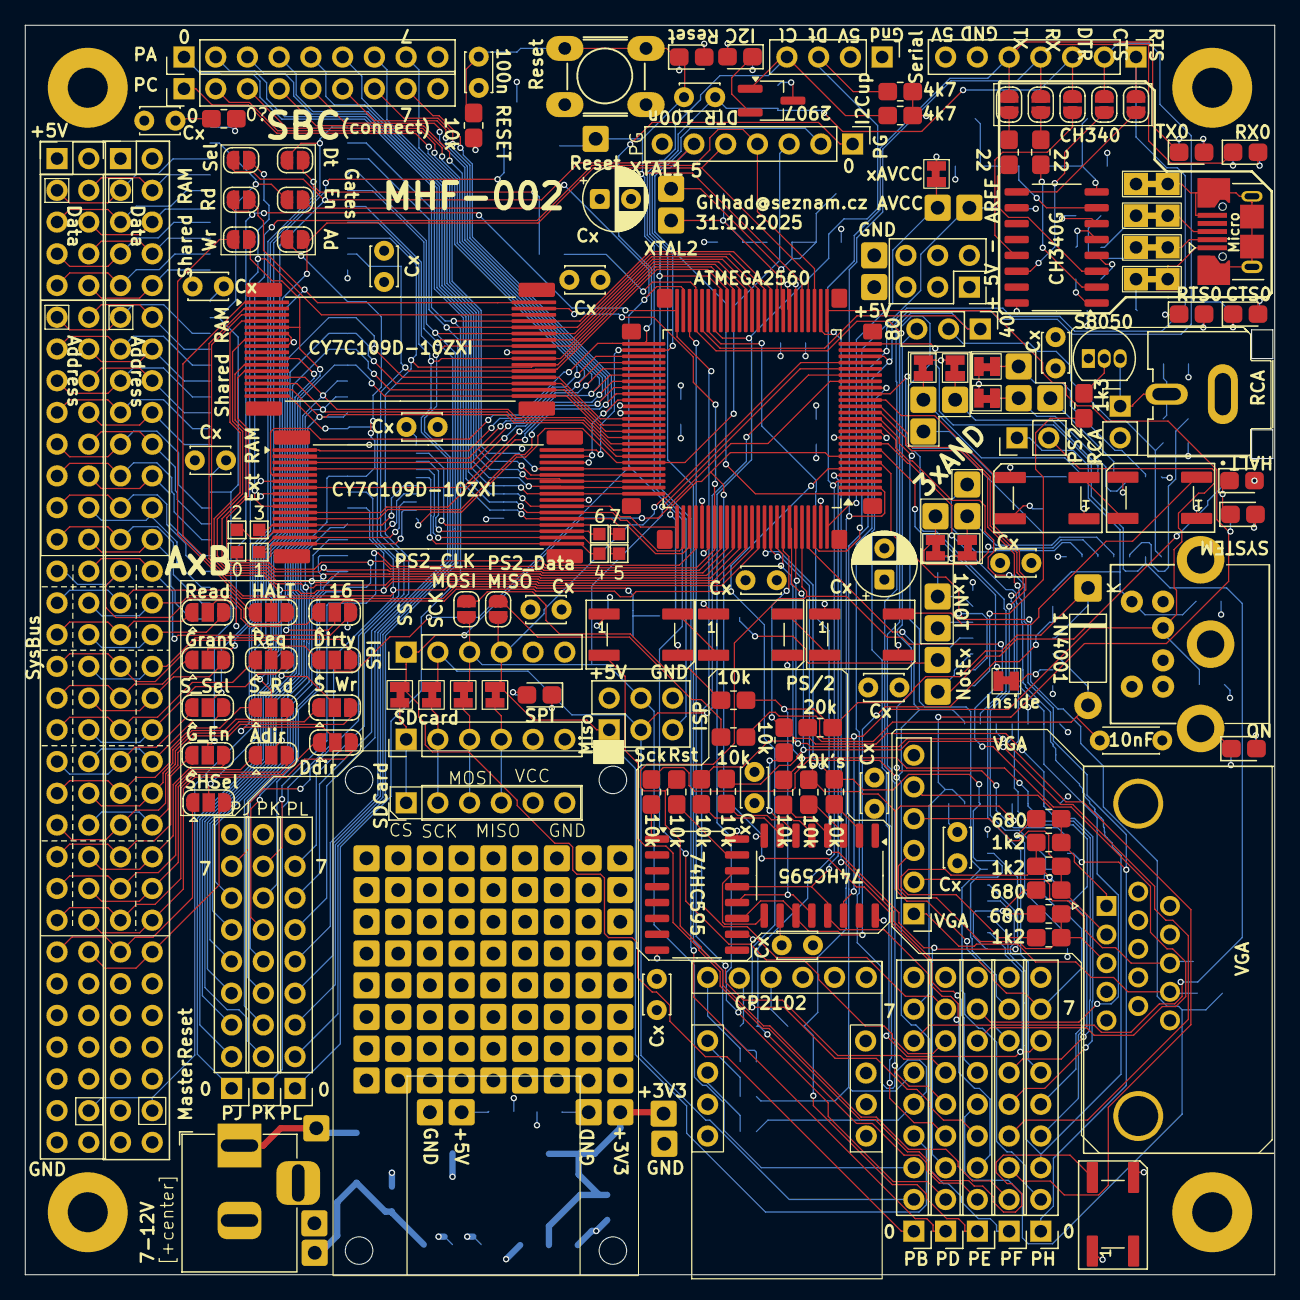
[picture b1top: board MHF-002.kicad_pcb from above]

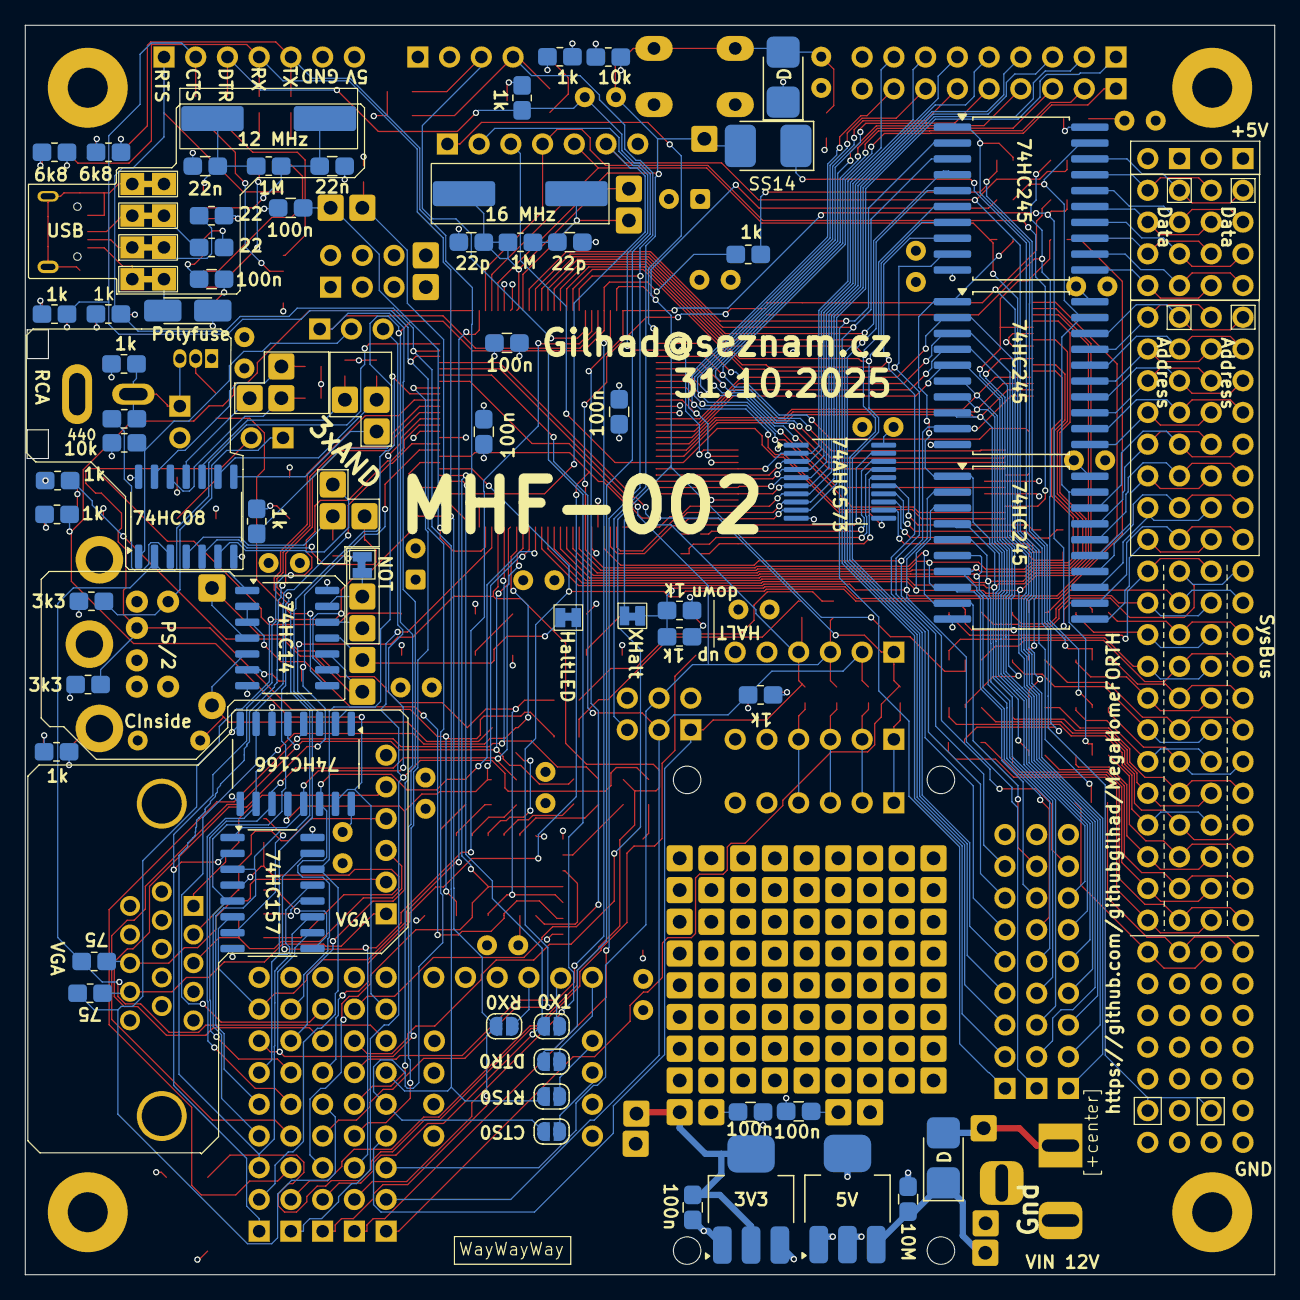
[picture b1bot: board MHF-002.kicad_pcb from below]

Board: 4 copper layers, 100.0 x 100.0 mm, 319 parts (67 on the bottom side), 255 nets.

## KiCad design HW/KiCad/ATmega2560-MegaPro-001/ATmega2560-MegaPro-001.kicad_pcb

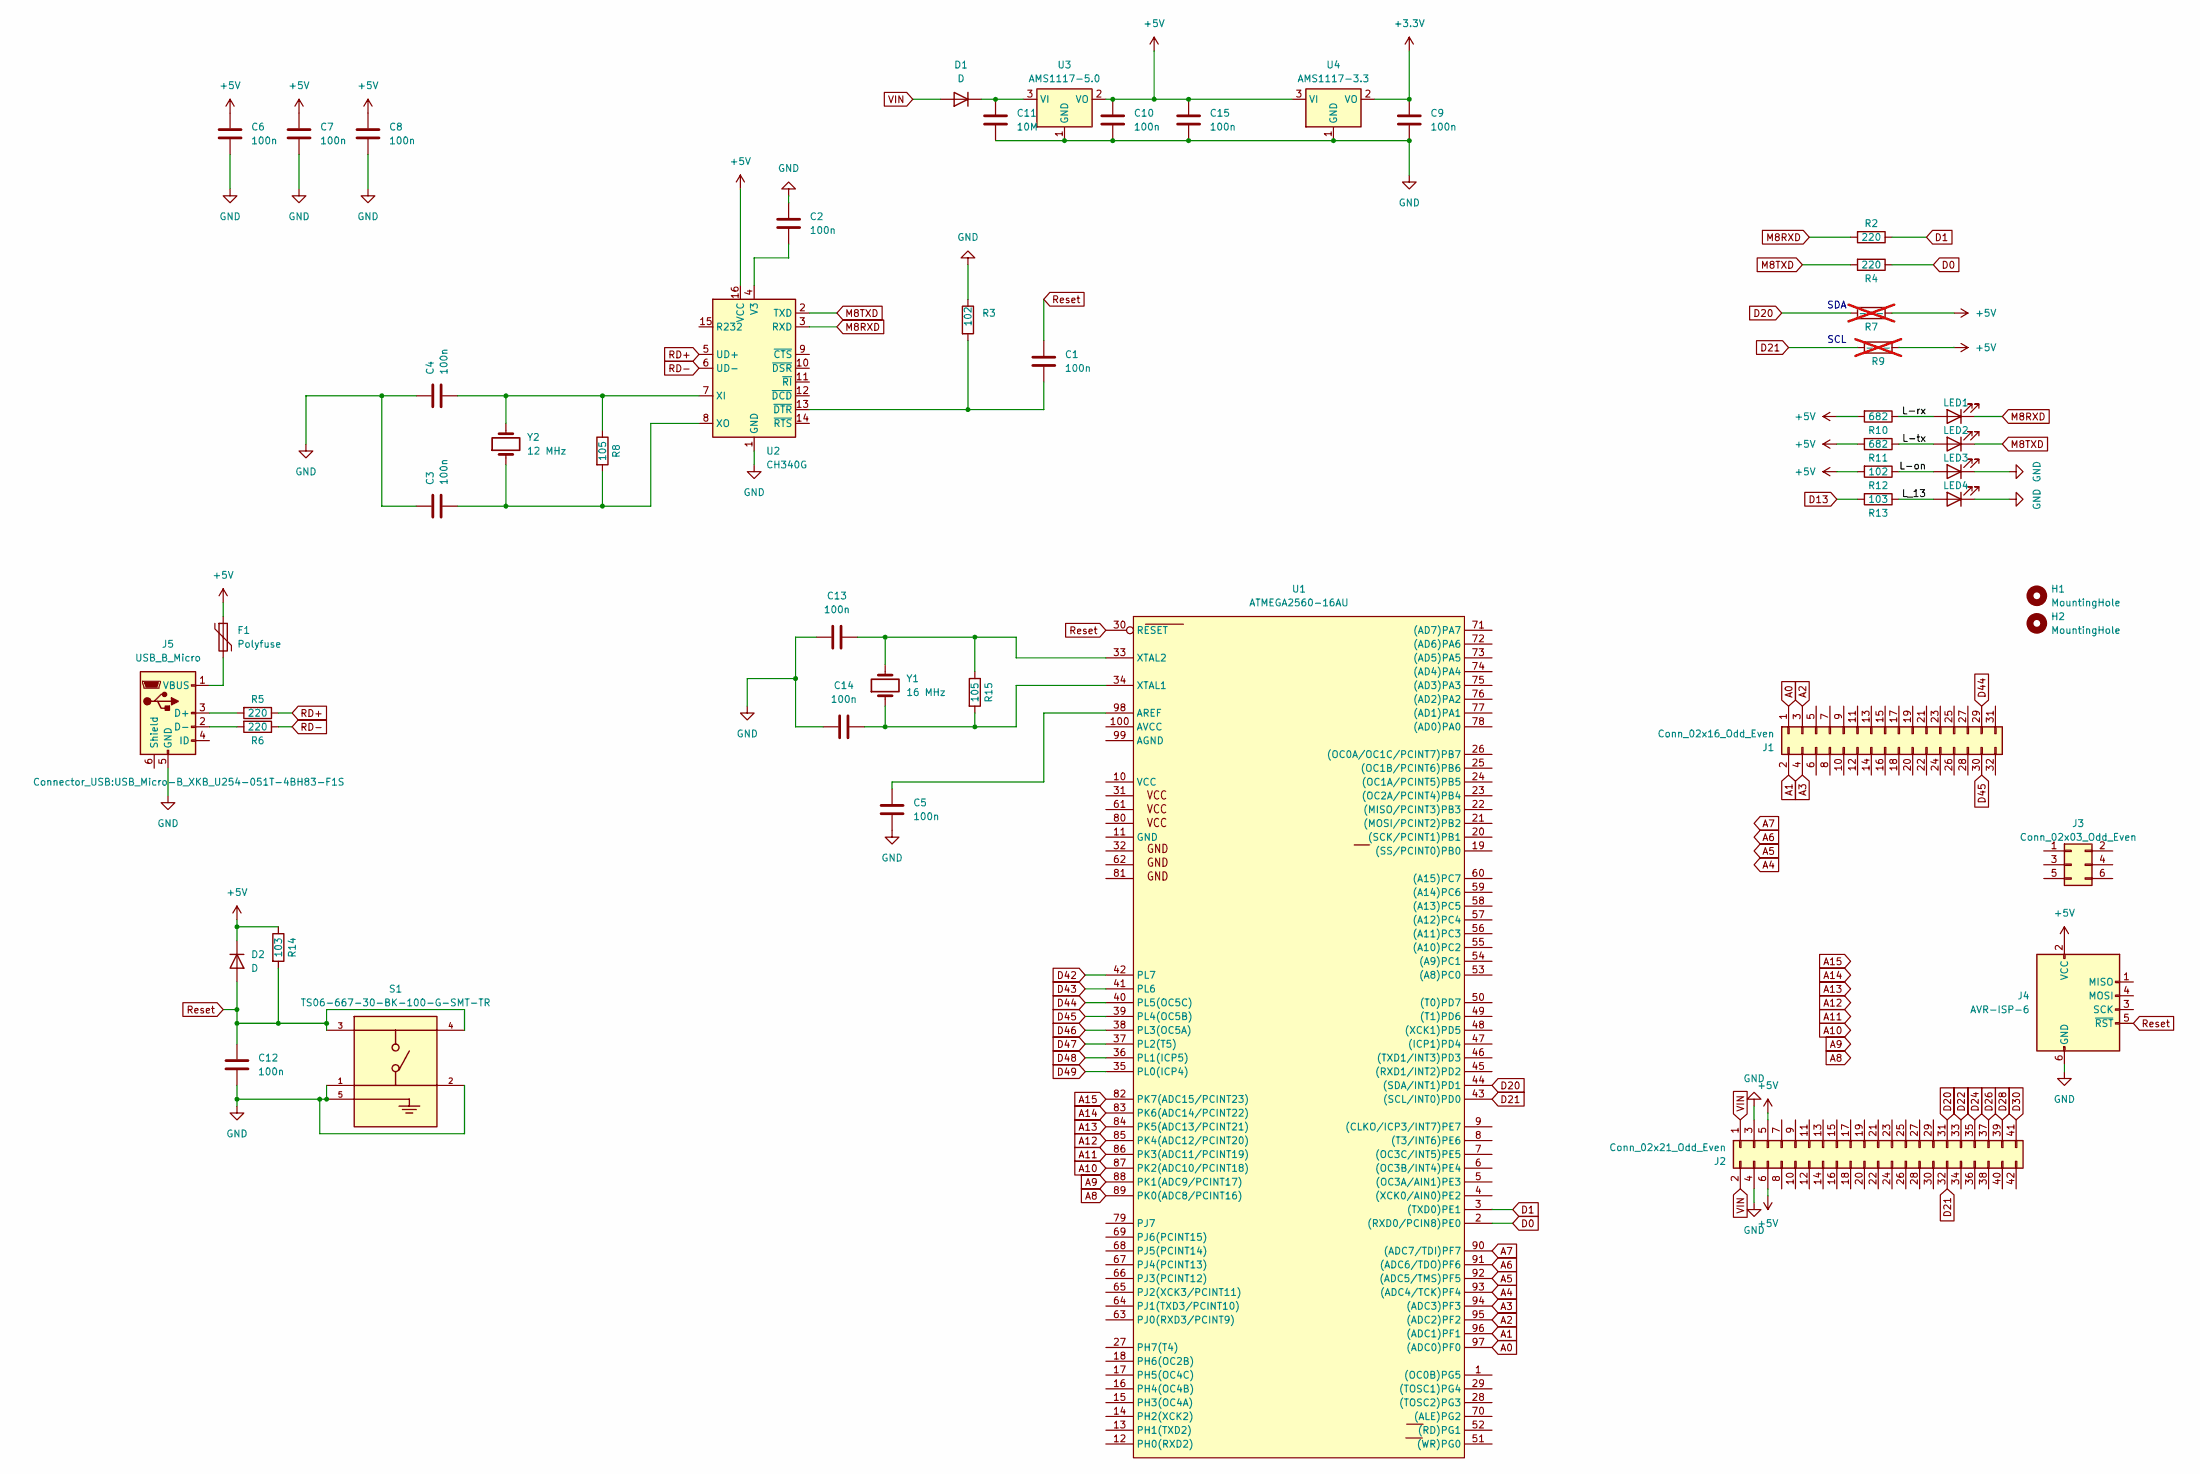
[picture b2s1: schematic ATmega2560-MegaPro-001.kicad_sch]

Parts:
C1, C2, C3, C4, C5, C6, C7, C8, C9, C10, C12, C13, C14, C15: 100n; C_0603_1608Metric
C11: 10M; C_1206_3216Metric
D1: D; D_1210_3225Metric
D2: D; D_1206_3216Metric
F1: Polyfuse; Fuse_1206_3216Metric_Pad1.42x1.75mm_HandSolder
H1, H2: MountingHole; MountingHole_3.2mm_M3
J1: Conn_02x16_Odd_Even; PinHeader_2x16_P2.54mm_Vertical
J2: Conn_02x21_Odd_Even; PinHeader_2x21_P2.54mm_Vertical
J3: Conn_02x03_Odd_Even; PinHeader_2x03_P2.54mm_Vertical
J4: AVR-ISP-6; PinHeader_2x03_P2.54mm_Vertical
J5: USB_B_Micro; USB_Micro-B_XKB_U254-051T-4BH83-F1S
LED1, LED2, LED3, LED4: LED; LED_0201_0603Metric
R2, R4, R5, R6: 220; R_0603_1608Metric
R3, R12: 102; R_0603_1608Metric
R7, R9: ---; R_0603_1608Metric; not fitted
R8, R15: 105; R_0603_1608Metric
R10, R11: 682; R_0603_1608Metric
R13, R14: 103; R_0603_1608Metric
S1: TS06-667-30-BK-100-G-SMT-TR; SW_TS06-667-30-BK-100-G-SMT-TR; PARTREV 1.0
U1: ATMEGA2560-16AU; TQFP-100_14x14mm_P0.5mm
U2: CH340G; SOIC-16_3.9x9.9mm_P1.27mm
U3: AMS1117-5.0; SOT-223-3_TabPin2
U4: AMS1117-3.3; SOT-223-3_TabPin2
Y1: 16 MHz; Crystal_SMD_HC49-SD
Y2: 12 MHz; Crystal_SMD_HC49-SD

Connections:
+3.3V: C9.1, U4.2 (VO)
+5V: C6.1, C7.1, C8.1, C10.1, C15.1, D2.1 (K), F1.1, J2.5, J2.6, J4.2 (VCC), R7.1, R9.1, R10.2, R11.2, R12.2, R14.1, U2.16 (VCC), U3.2 (VO), U4.3 (VI)
/L-on: LED3.2 (A), R12.1
/L-rx: LED1.2 (A), R10.1
/L-tx: LED2.2 (A), R11.1
/L_13: LED4.2 (A), R13.1
A0: J1.1, U1.97 ((ADC0)PF0)
A1: J1.2, U1.96 ((ADC1)PF1)
A2: J1.3, U1.95 ((ADC2)PF2)
A3: J1.4, U1.94 ((ADC3)PF3)
A4: U1.93 ((ADC4/TCK)PF4)
A5: U1.92 ((ADC5/TMS)PF5)
A6: U1.91 ((ADC6/TDO)PF6)
A7: U1.90 ((ADC7/TDI)PF7)
A8: U1.89 (PK0(ADC8/PCINT16))
A9: U1.88 (PK1(ADC9/PCINT17))
A10: U1.87 (PK2(ADC10/PCINT18))
A11: U1.86 (PK3(ADC11/PCINT19))
A12: U1.85 (PK4(ADC12/PCINT20))
A13: U1.84 (PK5(ADC13/PCINT21))
A14: U1.83 (PK6(ADC14/PCINT22))
A15: U1.82 (PK7(ADC15/PCINT23))
D0: R4.1, U1.2 ((RXD0/PCIN8)PE0)
D1: R2.1, U1.3 ((TXD0)PE1)
D13: R13.2
D20: J2.31, R7.2, U1.44 ((SDA/INT1)PD1)
D21: J2.32, R9.2, U1.43 ((SCL/INT0)PD0)
D22: J2.33
D24: J2.35
D26: J2.37
D28: J2.39
D30: J2.41
D42: U1.42 (PL7)
D43: U1.41 (PL6)
D44: J1.29, U1.40 (PL5(OC5C))
D45: J1.30, U1.39 (PL4(OC5B))
D46: U1.38 (PL3(OC5A))
D47: U1.37 (PL2(T5))
D48: U1.36 (PL1(ICP5))
D49: U1.35 (PL0(ICP4))
GND: C2.1, C3.1, C4.1, C5.2, C6.2, C7.2, C8.2, C9.2, C10.2, C11.2, C12.2, C13.1, C14.1, C15.2, J2.3, J2.4, J4.6 (GND), J5.5 (GND), LED3.1 (K), LED4.1 (K), R3.1, S1.1, S1.2, S1.5, U2.1 (GND), U3.1 (GND), U4.1 (GND)
M8RXD: LED1.1 (K), R2.2, U2.3 (RXD)
M8TXD: LED2.1 (K), R4.2, U2.2 (TXD)
unnamed: C11.1, D1.1 (K), U3.3 (VI)
unnamed: J5.3 (D+), R5.2
unnamed: J5.2 (D-), R6.2
unnamed: F1.2, J5.1 (VBUS)
unnamed: C5.1, U1.98 (AREF)
unnamed: C14.2, R15.2, U1.34 (XTAL1), Y1.1
unnamed: C13.2, R15.1, U1.33 (XTAL2), Y1.2
unnamed: C2.2, U2.4 (V3)
unnamed: C4.2, R8.1, U2.7 (XI), Y2.2
unnamed: C3.2, R8.2, U2.8 (XO), Y2.1
unnamed: C1.2, R3.2, U2.13 (~DTR)
RD+: R5.1, U2.5 (UD+)
RD-: R6.1, U2.6 (UD-)
Reset: C1.1, C12.1, D2.2 (A), J4.5 (~RST), R14.2, S1.3, S1.4, U1.30 (RESET)
VIN: D1.2 (A), J2.1, J2.2

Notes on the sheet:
SDA
SCL
